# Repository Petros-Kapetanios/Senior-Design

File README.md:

# Senior‑Design

Zip files of my Gerber files for each PCB I created for my watt‑meter project.

## Order of Creation

1. **Capacitor Test Board**
2. **Current Transformer Test Board**
3. **Voltage Transformer Test Board**
4. **Low Pass‑V1**
5. **Low Pass‑V2**
6. **Final_Board‑Analog‑v1**
7. **Final_Board‑Analog‑v2**
8. **Final_Board‑Analog‑v3**
9. **Final_Board‑v1**
10. **Final_Board‑v2**
11. **Final_Board‑v3‑Triple‑Transformer**
12. **Final_Board‑v3B**
13. **Final_Board‑v3B‑Mark’s Copy**
14. **Final_Board‑v3C**
15. **Final_Board‑v3D**

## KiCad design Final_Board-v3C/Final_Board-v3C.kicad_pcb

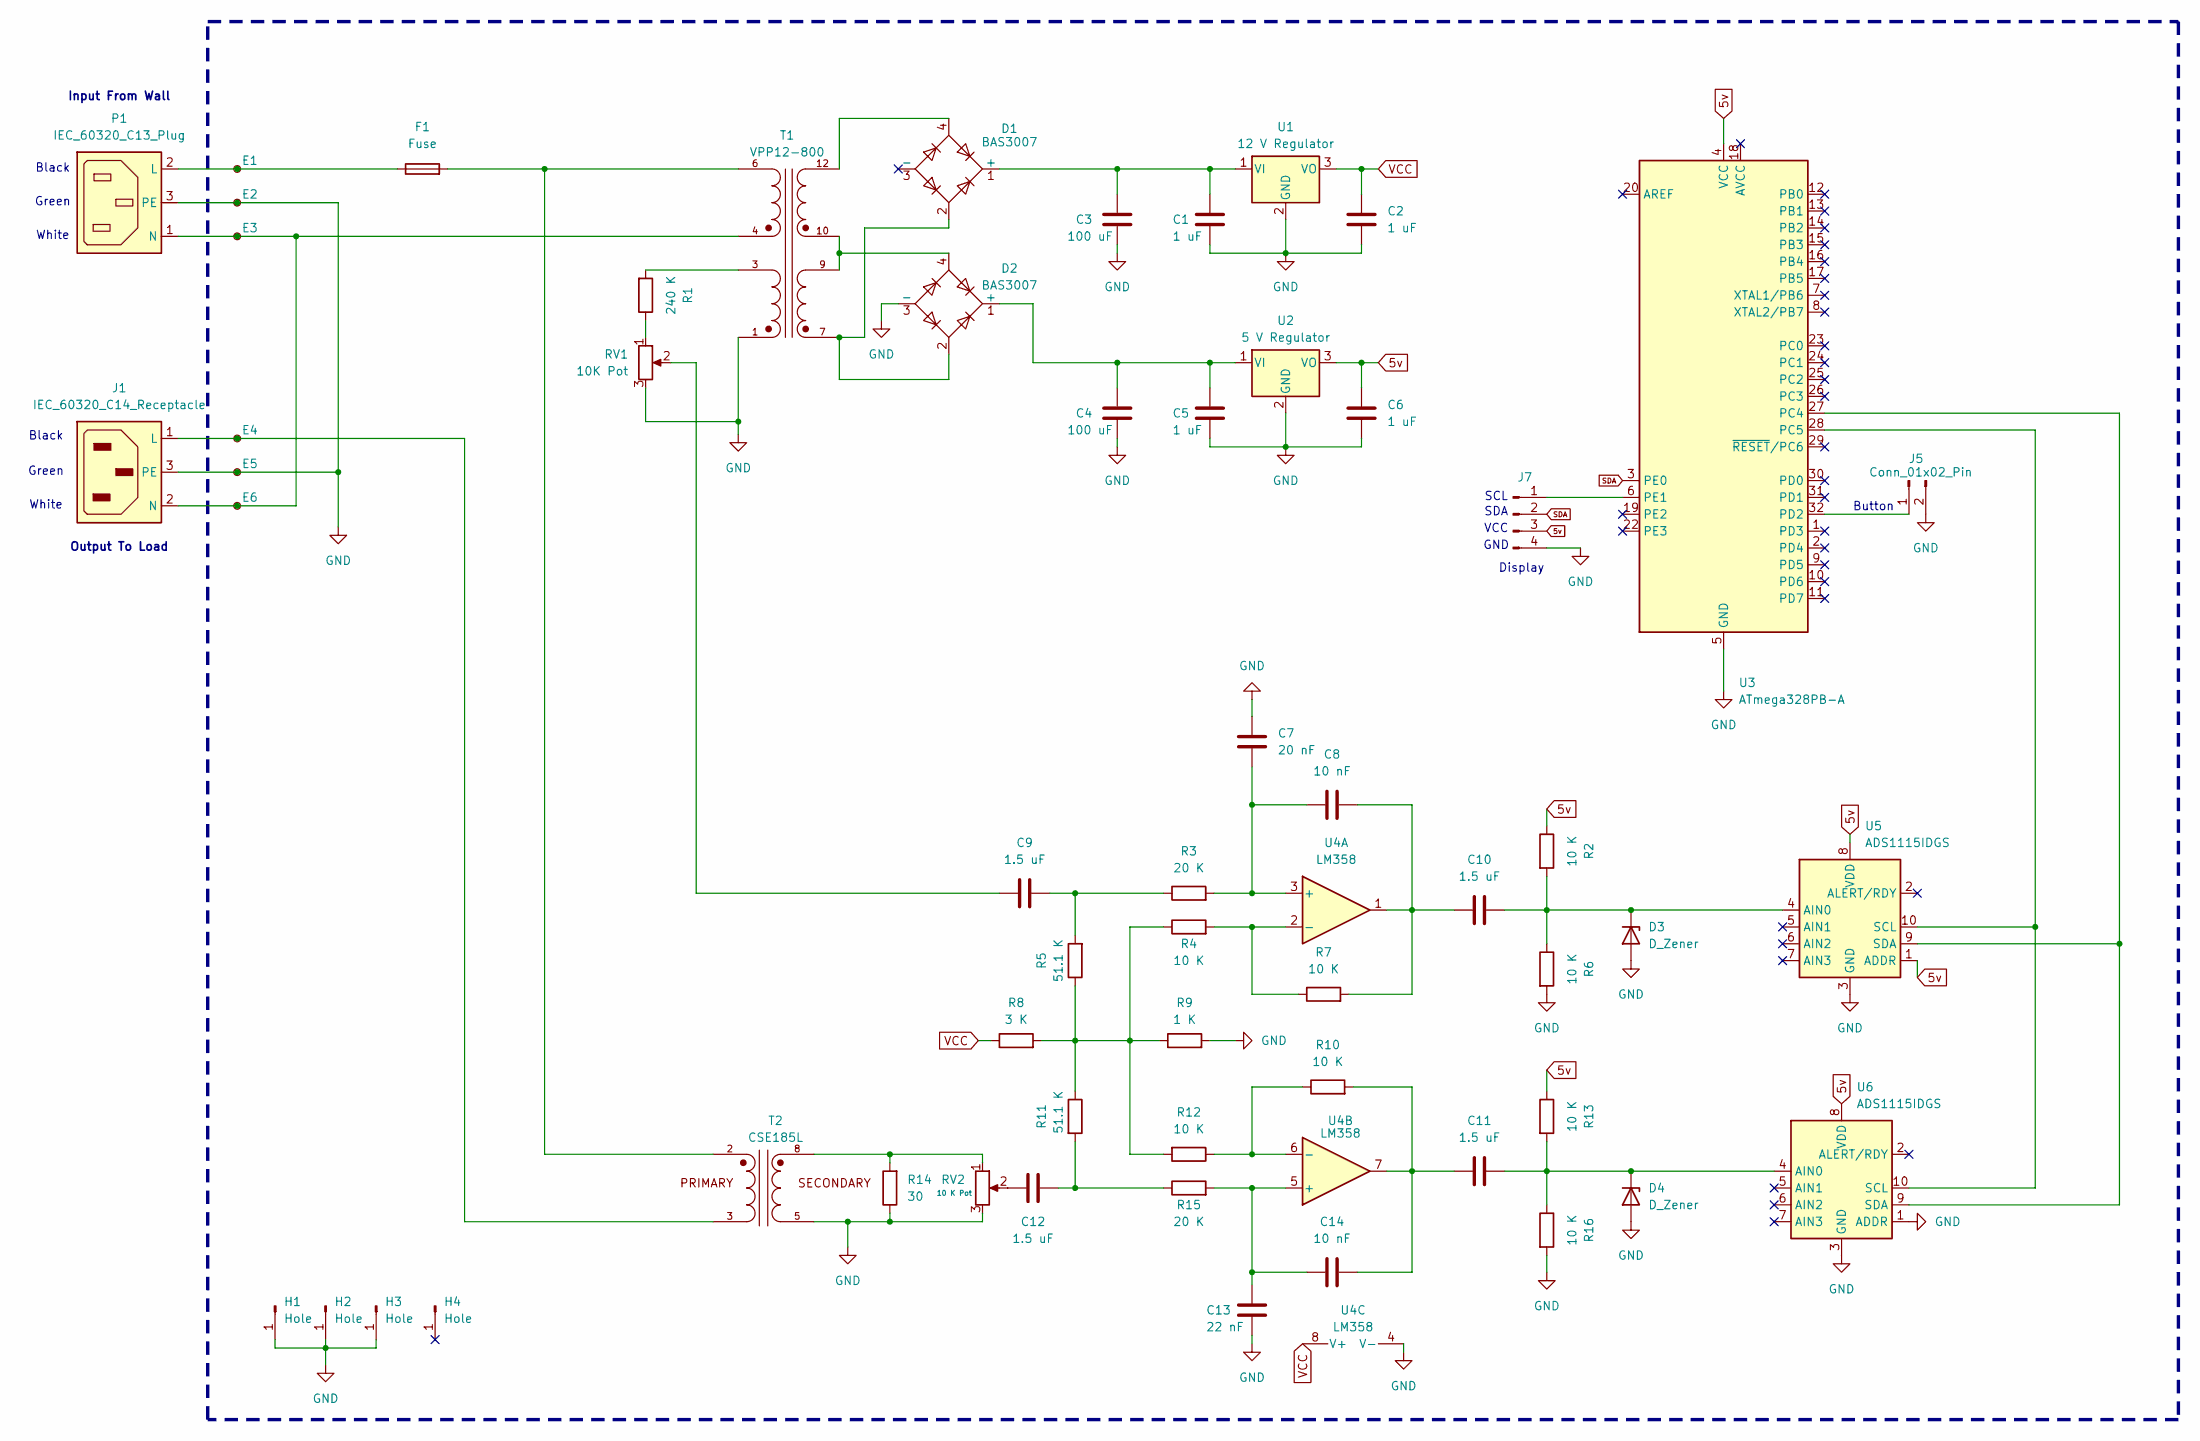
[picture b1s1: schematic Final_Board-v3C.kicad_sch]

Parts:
C1, C2, C5, C6: 1 uF; C_0805_2012Metric_Pad1.18x1.45mm_HandSolder
C3, C4: 100 uF; CP_Radial_D10.0mm_P5.00mm
C7: 20 nF; C_0805_2012Metric_Pad1.18x1.45mm_HandSolder
C8, C14: 10 nF; C_0805_2012Metric_Pad1.18x1.45mm_HandSolder
C9, C10, C11, C12: 1.5 uF; C_0805_2012Metric_Pad1.18x1.45mm_HandSolder
C13: 22 nF; C_0805_2012Metric_Pad1.18x1.45mm_HandSolder
D1, D2: BAS3007; SOT-143
D3, D4: D_Zener; D_SOD-123
E1, E2, E3, E4, E5, E6: TestPoint_Small; MountingHole_2.2mm_M2_ISO7380_Pad_TopBottom
F1: Fuse; Fuseholder_Keystone_3555-2
H1, H2, H3, H4: Hole; SolderWire-2sqmm_1x01_D2mm_OD3.9mm
J1: IEC_60320_C14_Receptacle
J5: Conn_01x02_Pin; PinHeader_1x02_P2.54mm_Vertical
J7: Conn_01x04_Pin; PinHeader_1x04_P2.54mm_Vertical
P1: IEC_60320_C13_Plug
R1: 240 K; R_1210_3225Metric
R2, R4, R6, R7, R10, R12, R13, R16: 10 K; R_0603_1608Metric
R3, R15: 20 K; R_0603_1608Metric
R5, R11: 51.1 K; R_0603_1608Metric
R8: 3 K; R_0603_1608Metric
R9: 1 K; R_0603_1608Metric
R14: 30; R_0603_1608Metric
RV1: 10K Pot; Potentiometer_Bourns_3296W_Vertical
RV2: 10 K Pot; Potentiometer_Bourns_3296W_Vertical
T1: VPP12-800; XFMR_VPP12-800
T2: CSE185L; XFMR_CSE185L; PARTREV N/A
U1: 12 V Regulator; TO-220-3_Vertical
U2: 5 V Regulator; TO-220-3_Vertical
U3: ATmega328PB-A; TQFP-32_7x7mm_P0.8mm
U4: LM358; DIP-8_W7.62mm_Socket
U5, U6: ADS1115IDGS; TSSOP-10_3x3mm_P0.5mm

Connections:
5v: C6.1, J7.3, R2.1, R13.1, U2.3 (VO), U3.4 (VCC), U5.1 (ADDR), U5.8 (VDD), U6.8 (VDD)
GND: C1.2, C2.2, C3.2, C4.2, C5.2, C6.2, C7.2, C13.1, D2.3 (-), D3.2 (A), D4.2 (A), E2.1, E5.1, H1.1, H2.1, H3.1, J1.3 (PE), J5.2, J7.4, P1.3 (PE), R6.2, R9.2, R14.1, R16.2, RV1.3, RV2.3, T1.1, T2.5, U1.2 (GND), U2.2 (GND), U3.5 (GND), U3.21 (GND), U4.4 (V-), U5.3 (GND), U6.1 (ADDR), U6.3 (GND)
unnamed: C9.1, RV1.2
unnamed: C9.2, R3.1, R5.2
unnamed: C8.2, C10.1, R7.2, U4.1
unnamed: C11.1, C14.2, R10.2, U4.7
unnamed: C12.1, RV2.2
unnamed: C12.2, R11.2, R15.1
unnamed: C1.1, C3.1, D1.1 (+), U1.1 (VI)
unnamed: D1.2, D2.2, T1.7
unnamed: D1.4, T1.12
unnamed: C4.1, C5.1, D2.1 (+), U2.1 (VI)
unnamed: D2.4, T1.9, T1.10
unnamed: C10.2, D3.1 (K), R2.2, R6.1, U5.4 (AIN0)
unnamed: C11.2, D4.1 (K), R13.2, R16.1, U6.4 (AIN0)
unnamed: F1.2, T1.6, T2.2
unnamed: E4.1, J1.1 (L), T2.3
unnamed: E3.1, E6.1, J1.2 (N), P1.1 (N), T1.4
unnamed: J5.1, U3.32 (PD2)
unnamed: J7.1, U3.6 (PE1)
unnamed: E1.1, F1.1, P1.2 (L)
unnamed: R1.1, RV1.1
unnamed: R1.2, T1.3
unnamed: R4.1, R5.1, R8.2, R9.1, R11.1, R12.2
unnamed: R14.2, RV2.1, T2.8
unnamed: U3.27 (PC4), U5.9 (SDA), U6.9 (SDA)
unnamed: U3.28 (PC5), U5.10 (SCL), U6.10 (SCL)
unnamed: C7.1, C8.1, R3.2, U4.3 (+)
unnamed: R4.2, R7.1, U4.2 (-)
unnamed: C13.2, C14.1, R15.2, U4.5 (+)
unnamed: R10.1, R12.1, U4.6 (-)
SDA: J7.2, U3.3 (PE0)
VCC: C2.1, R8.1, U1.3 (VO), U4.8 (V+)

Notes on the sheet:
Black
SDA
Green
Button
White
SCL
Input From Wall
VCC
GND
Display
Output To Load

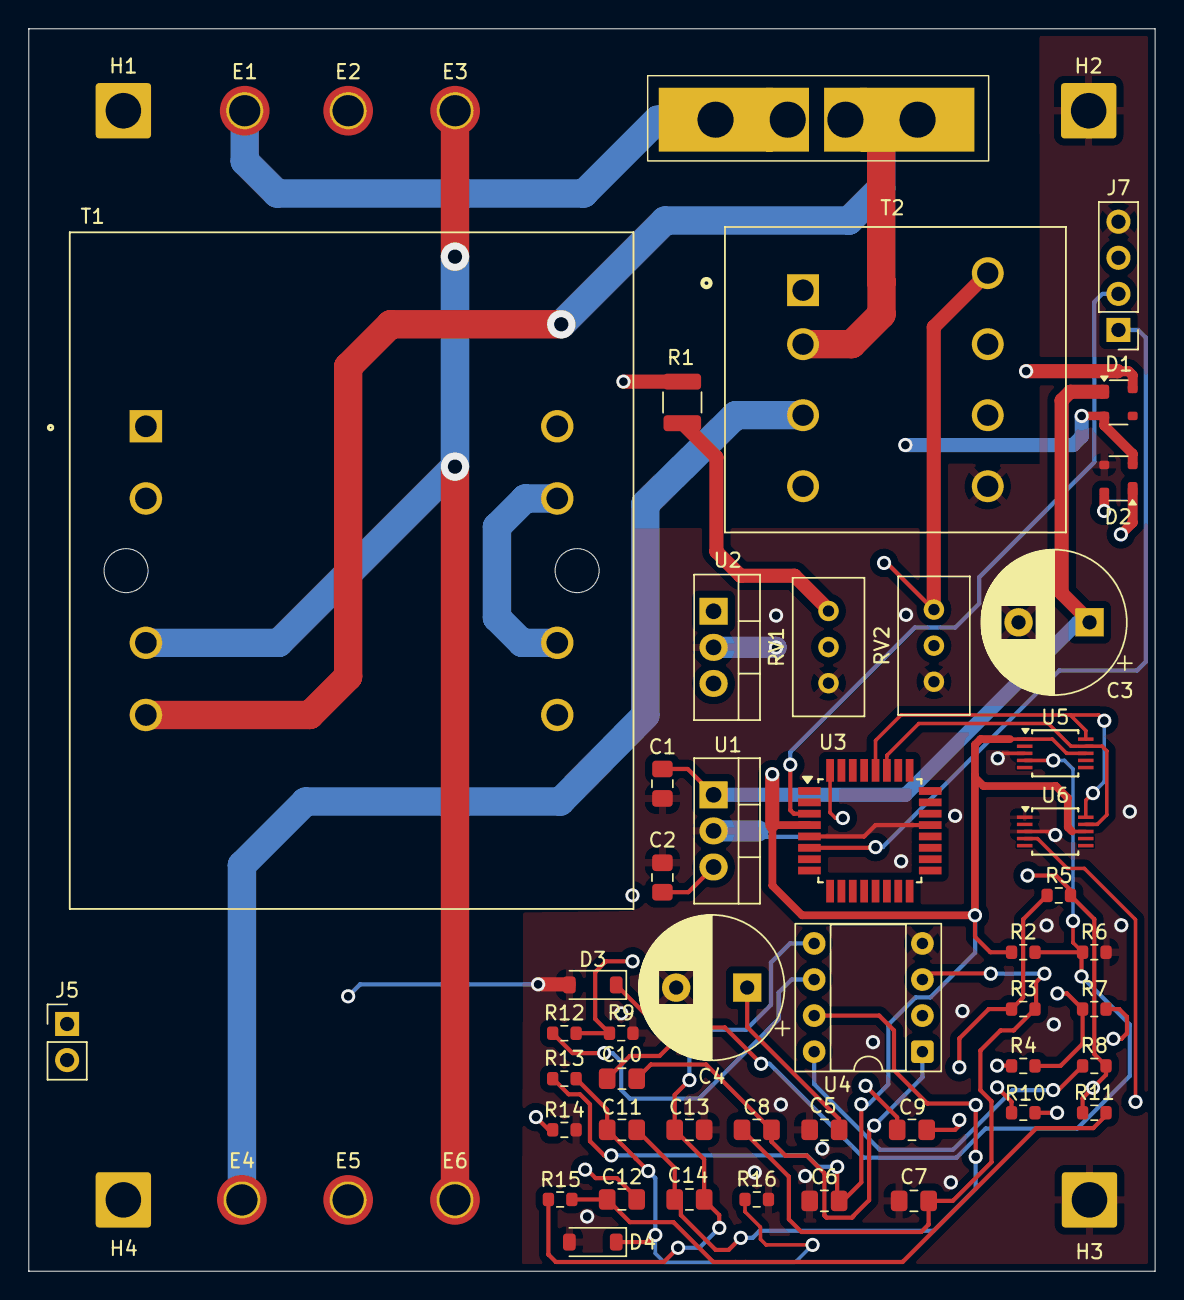
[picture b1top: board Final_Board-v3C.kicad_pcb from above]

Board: 4 copper layers, 79.3 x 87.5 mm, 57 parts (0 on the bottom side), 33 nets.

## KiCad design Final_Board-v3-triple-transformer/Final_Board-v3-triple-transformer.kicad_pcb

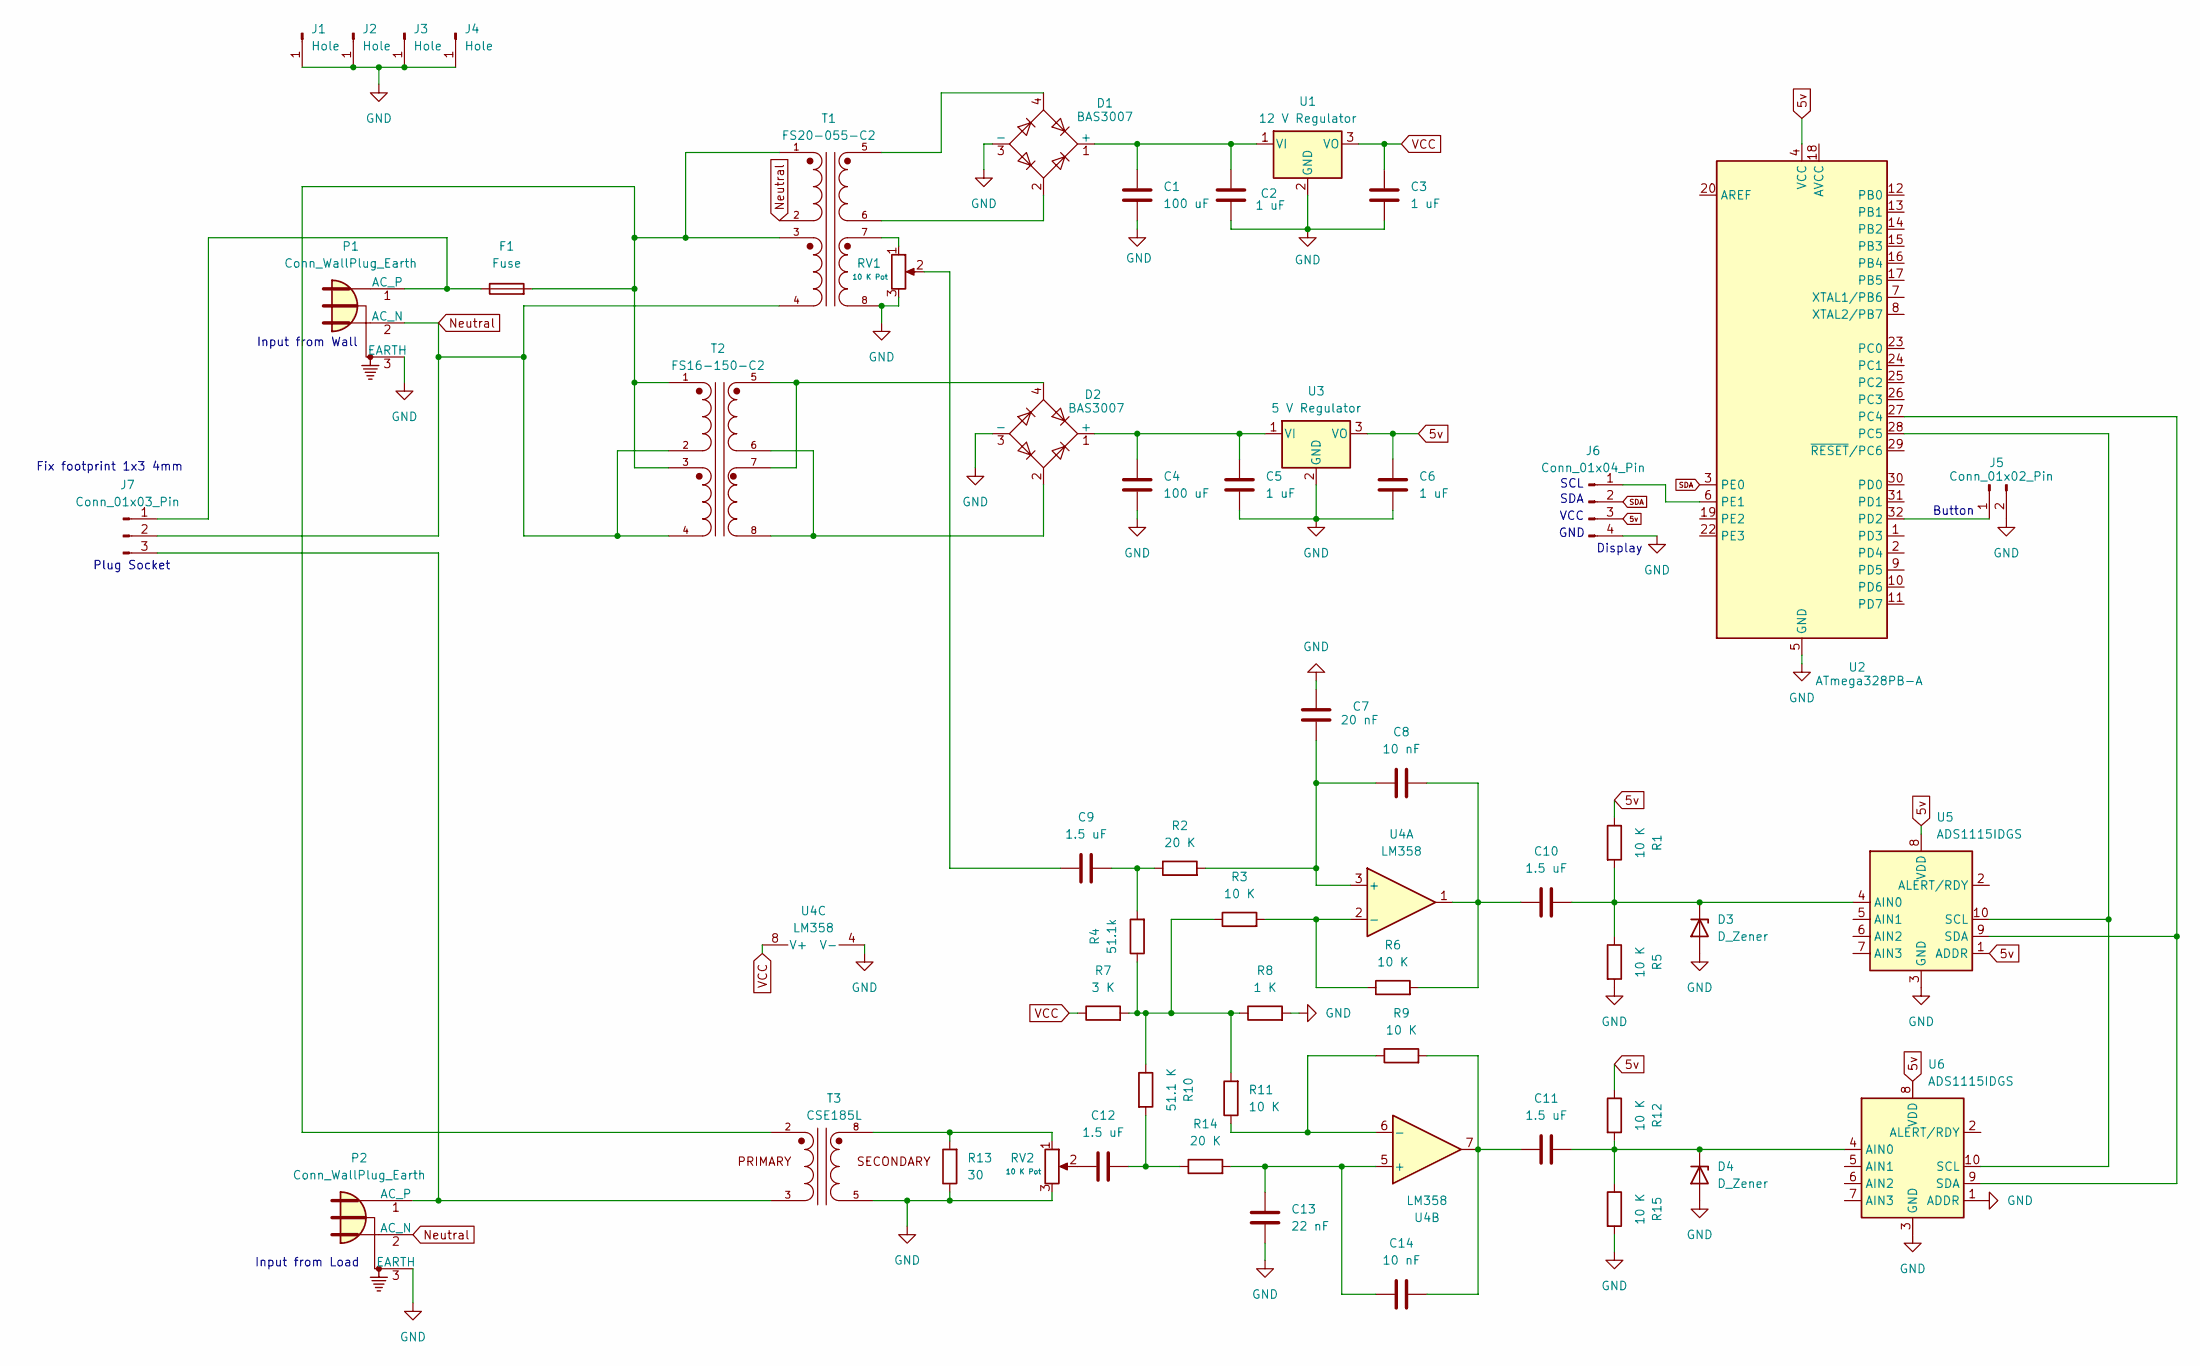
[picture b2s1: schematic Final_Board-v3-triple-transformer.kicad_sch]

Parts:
C1, C4: 100 uF; CP_Radial_D10.0mm_P5.00mm
C2, C3, C5, C6: 1 uF; C_0805_2012Metric_Pad1.18x1.45mm_HandSolder
C7: 20 nF; C_0805_2012Metric_Pad1.18x1.45mm_HandSolder
C8, C14: 10 nF; C_0805_2012Metric_Pad1.18x1.45mm_HandSolder
C9, C10, C11, C12: 1.5 uF; C_0805_2012Metric_Pad1.18x1.45mm_HandSolder
C13: 22 nF; C_0805_2012Metric_Pad1.18x1.45mm_HandSolder
D1, D2: BAS3007; SOT-143
D3, D4: D_Zener; D_SOD-123
F1: Fuse; Fuseholder_Keystone_3555-2
J1, J2, J3, J4: Hole; SolderWire-2sqmm_1x01_D2mm_OD3.9mm
J5: Conn_01x02_Pin; PinHeader_1x02_P2.00mm_Vertical
J6: Conn_01x04_Pin; PinHeader_1x04_P2.00mm_Vertical
J7: Conn_01x03_Pin; SolderWire-0.15sqmm_1x03_P4mm_D0.5mm_OD1.5mm
P1, P2: Conn_WallPlug_Earth
R1, R3, R5, R6, R9, R11, R12, R15: 10 K; R_0603_1608Metric
R2, R14: 20 K; R_0603_1608Metric
R4: 51.1k; R_0603_1608Metric
R7: 3 K; R_0603_1608Metric
R8: 1 K; R_0603_1608Metric
R10: 51.1 K; R_0603_1608Metric
R13: 30; R_0603_1608Metric
RV1, RV2: 10 K Pot; Potentiometer_Bourns_3296W_Vertical
T1: FS20-055-C2; XFMR_FS20-055-C2; PARTREV N/A
T2: FS16-150-C2; XFMR_FS16-150-C2; PARTREV N/A
T3: CSE185L; XFMR_CSE185L; PARTREV N/A
U1: 12 V Regulator; TO-220-3_Vertical
U2: ATmega328PB-A; TQFP-32_7x7mm_P0.8mm
U3: 5 V Regulator; TO-220-3_Vertical
U4: LM358; DIP-8_W7.62mm
U5, U6: ADS1115IDGS; VSSOP-10_3x3mm_P0.5mm

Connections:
5v: C6.1, J6.3, R1.1, R12.1, U2.4 (VCC), U3.3 (VO), U5.1 (ADDR), U5.8 (VDD), U6.8 (VDD)
GND: C1.2, C2.2, C3.2, C4.2, C5.2, C6.2, C7.2, C13.1, D1.3 (-), D2.3 (-), D3.2 (A), D4.2 (A), J1.1, J2.1, J3.1, J4.1, J5.2, J6.4, P1.3 (EARTH), P2.3 (EARTH), R5.2, R8.2, R13.1, R15.2, RV1.3, RV2.3, T1.8, T3.5, U1.2 (GND), U2.5 (GND), U2.21 (GND), U3.2 (GND), U4.4 (V-), U5.3 (GND), U6.1 (ADDR), U6.3 (GND)
unnamed: C9.1, RV1.2
unnamed: C9.2, R2.1, R4.2
unnamed: C8.2, C10.1, R6.2, U4.1
unnamed: C11.1, C14.2, R9.2, U4.7
unnamed: C12.1, RV2.2
unnamed: C12.2, R10.2, R14.1
unnamed: C1.1, C2.1, D1.1 (+), U1.1 (VI)
unnamed: D1.2, T1.6
unnamed: D1.4, T1.5
unnamed: C4.1, C5.1, D2.1 (+), U3.1 (VI)
unnamed: D2.2, T2.6, T2.8
unnamed: D2.4, T2.5, T2.7
unnamed: C10.2, D3.1 (K), R1.2, R5.1, U5.4 (AIN0)
unnamed: C11.2, D4.1 (K), R12.2, R15.1, U6.4 (AIN0)
unnamed: F1.2, T1.1, T1.3, T2.1, T2.3, T3.2
unnamed: J5.1, U2.32 (PD2)
unnamed: J6.1, U2.6 (PE1)
unnamed: F1.1, J7.1, P1.1 (AC_P)
unnamed: J7.3, P2.1 (AC_P), T3.3
unnamed: R3.1, R4.1, R7.2, R8.1, R10.1, R11.2
unnamed: R13.2, RV2.1, T3.8
unnamed: RV1.1, T1.7
unnamed: U2.27 (PC4), U5.9 (SDA), U6.9 (SDA)
unnamed: U2.28 (PC5), U5.10 (SCL), U6.10 (SCL)
unnamed: C7.1, C8.1, R2.2, U4.3 (+)
unnamed: R3.2, R6.1, U4.2 (-)
unnamed: C13.2, C14.1, R14.2, U4.5 (+)
unnamed: R9.1, R11.1, U4.6 (-)
Neutral: J7.2, P1.2 (AC_N), P2.2 (AC_N), T1.2, T1.4, T2.2, T2.4
SDA: J6.2, U2.3 (PE0)
VCC: C3.1, R7.1, U1.3 (VO), U4.8 (V+)

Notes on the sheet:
SDA
Plug Socket
Button
SCL
Input from Wall
VCC
GND
Fix footprint 1x3 4mm
Display
Input from Load

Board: 2 copper layers, 52 parts (1 on the bottom side), 33 nets, no tracks yet.

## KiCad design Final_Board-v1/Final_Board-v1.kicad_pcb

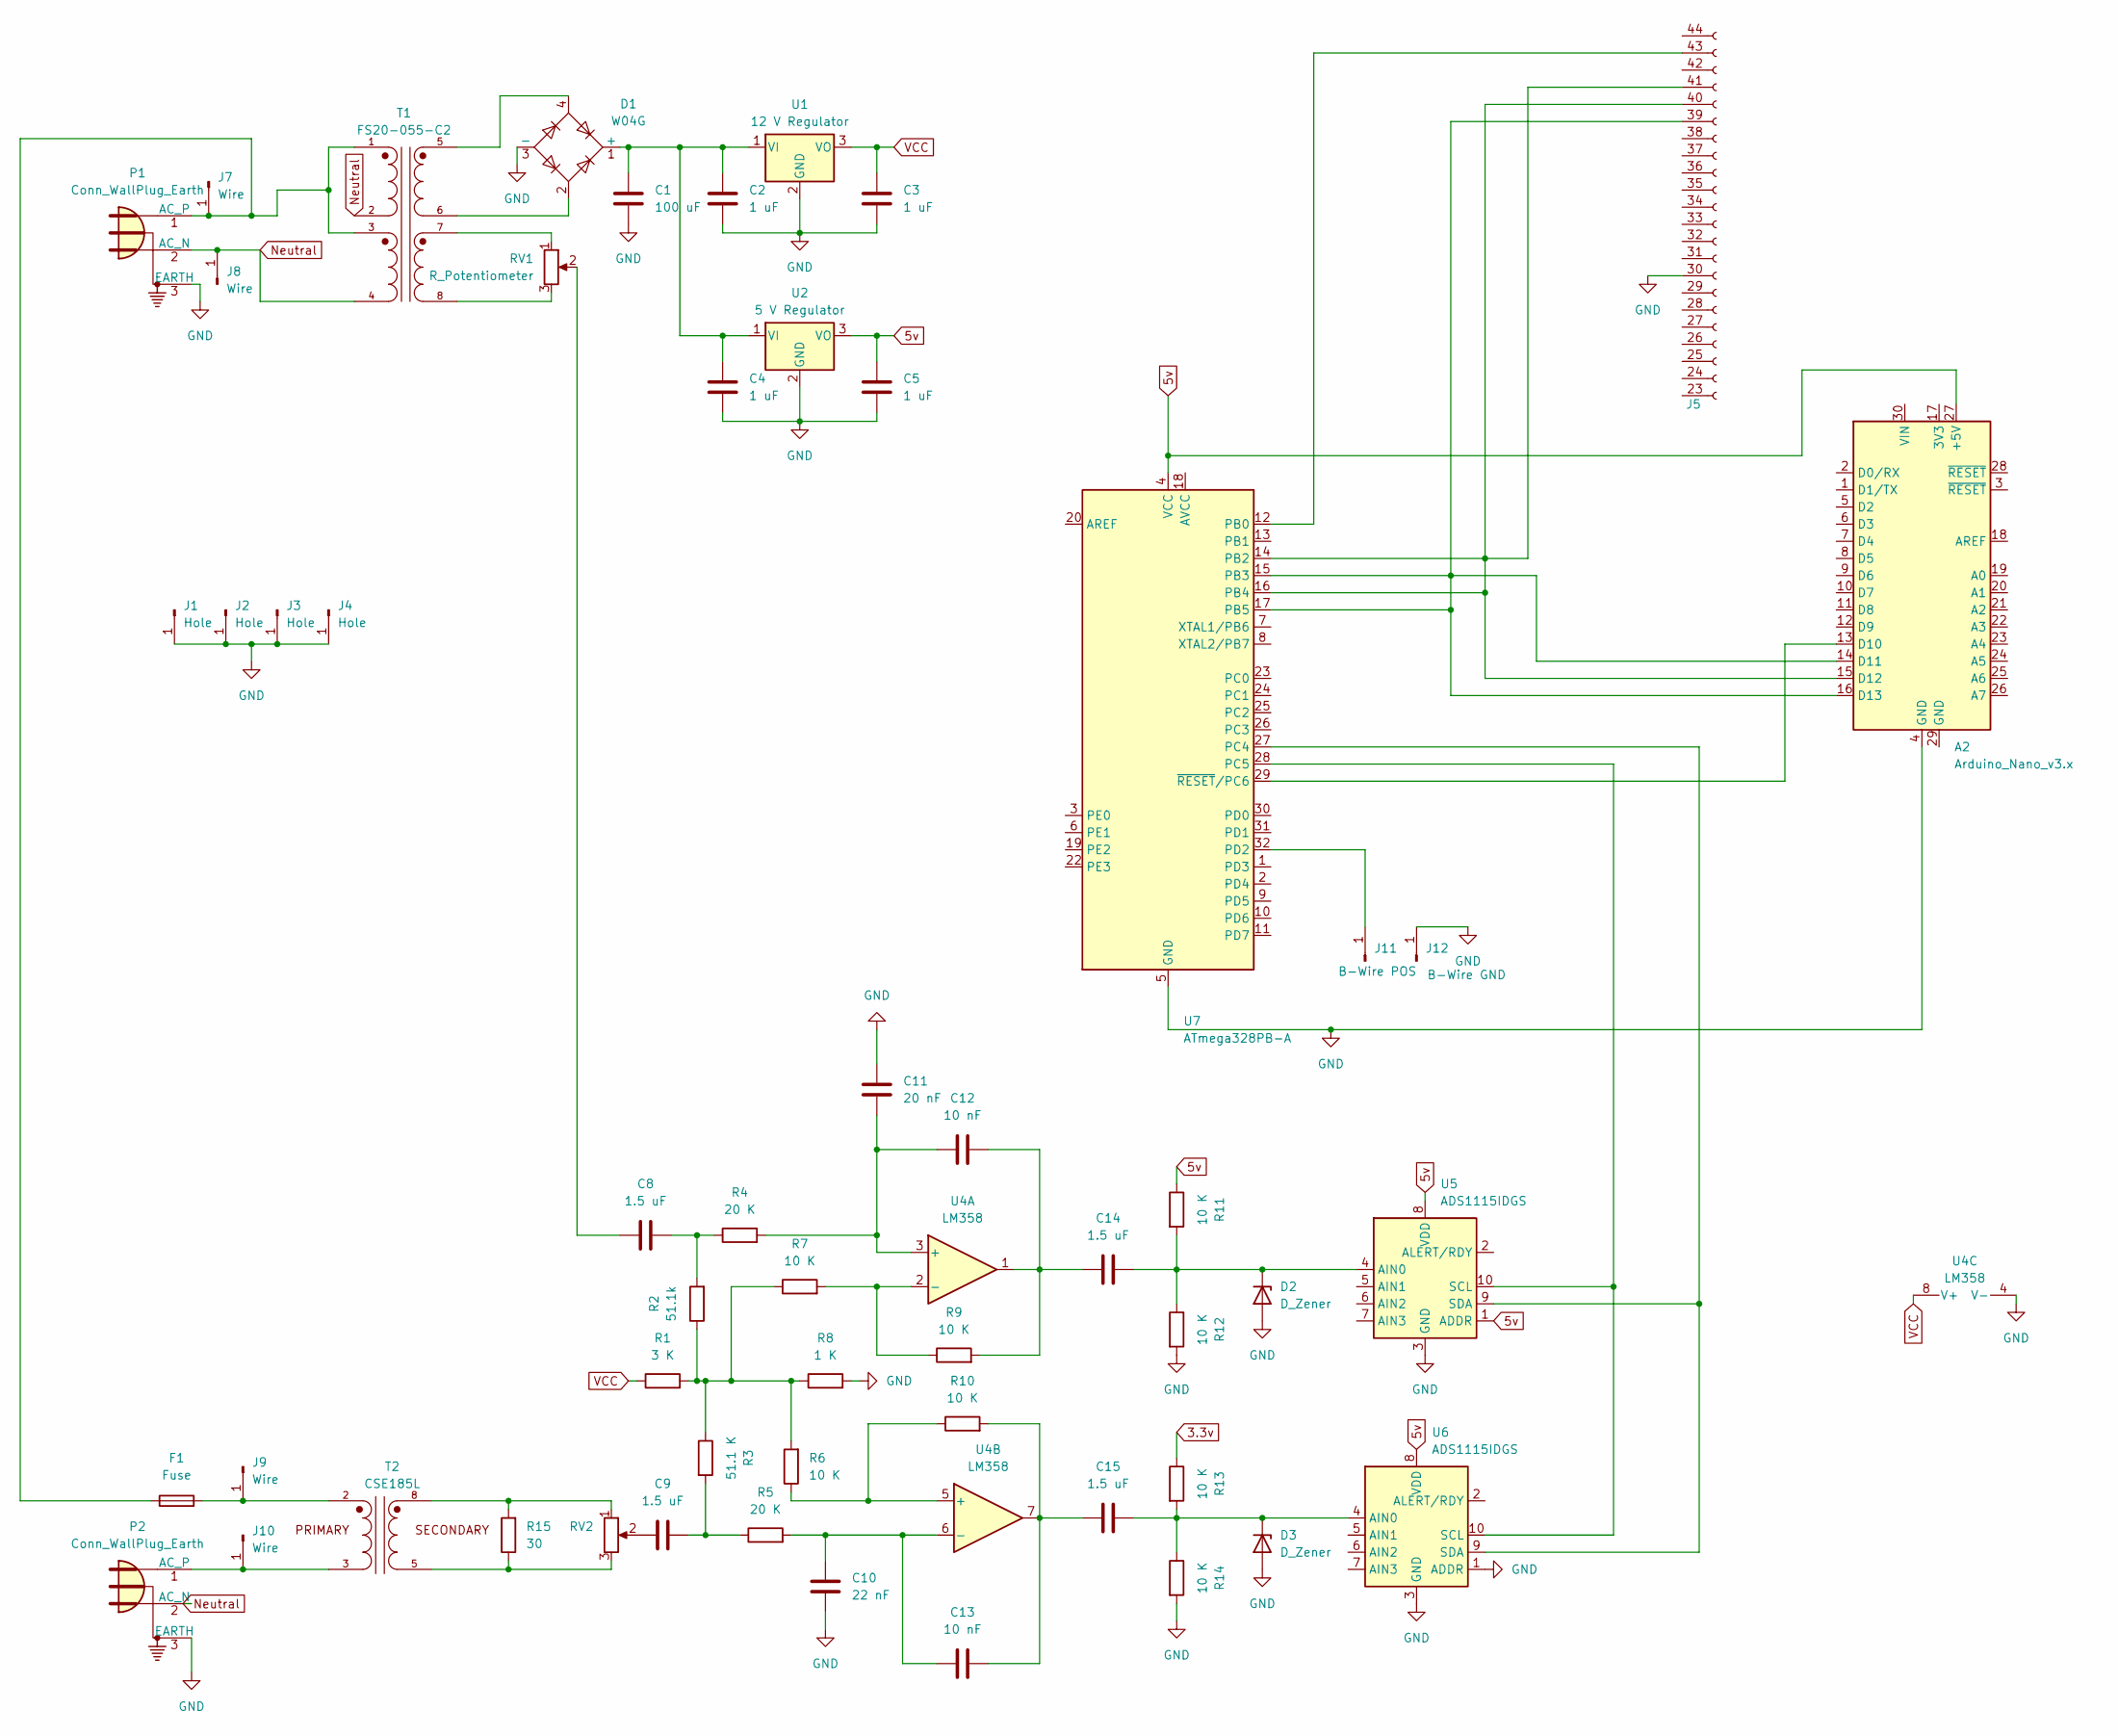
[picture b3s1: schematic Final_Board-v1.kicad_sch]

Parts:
A2: Arduino_Nano_v3.x; Arduino_Nano
C1: 100 uF; CP_Radial_D10.0mm_P5.00mm
C2, C3, C4, C5: 1 uF; C_Disc_D4.7mm_W2.5mm_P5.00mm
C8, C9, C14, C15: 1.5 uF; C_Rect_L7.2mm_W5.5mm_P5.00mm_FKS2_FKP2_MKS2_MKP2
C10: 22 nF; C_Disc_D4.7mm_W2.5mm_P5.00mm
C11: 20 nF; C_Rect_L7.5mm_W6.5mm_P5.00mm
C12, C13: 10 nF; C_Disc_D4.7mm_W2.5mm_P5.00mm
D1: W04G; Diode_Bridge_Round_D9.8mm
D2, D3: D_Zener; D_A-405_P10.16mm_Horizontal
F1: Fuse
J1, J2, J3, J4: Hole; SolderWire-2sqmm_1x01_D2mm_OD3.9mm
J5: Conn_01x22_Socket; PinSocket_1x22_P2.54mm_Vertical
J7, J8, J9, J10: Wire; SolderWire-2sqmm_1x01_D2mm_OD3.9mm
J11: B-Wire POS; SolderWire-2sqmm_1x01_D2mm_OD3.9mm
J12: B-Wire GND; SolderWire-2sqmm_1x01_D2mm_OD3.9mm
P1, P2: Conn_WallPlug_Earth
R1: 3 K; R_Axial_DIN0207_L6.3mm_D2.5mm_P10.16mm_Horizontal
R2: 51.1k; R_Axial_DIN0207_L6.3mm_D2.5mm_P10.16mm_Horizontal
R3: 51.1 K; R_Axial_DIN0207_L6.3mm_D2.5mm_P10.16mm_Horizontal
R4, R5: 20 K; R_Axial_DIN0207_L6.3mm_D2.5mm_P10.16mm_Horizontal
R6, R7, R9, R10, R14: 10 K; R_Axial_DIN0207_L6.3mm_D2.5mm_P10.16mm_Horizontal
R8: 1 K; R_1206_3216Metric
R11, R12, R13: 10 K; R_1206_3216Metric
R15: 30; R_Axial_DIN0207_L6.3mm_D2.5mm_P10.16mm_Horizontal
RV1, RV2: R_Potentiometer; Potentiometer_ACP_CA6-H2,5_Horizontal
T1: FS20-055-C2; XFMR_FS20-055-C2; PARTREV N/A
T2: CSE185L; XFMR_CSE185L; PARTREV N/A
U1: 12 V Regulator; TO-220-3_Vertical
U2: 5 V Regulator; TO-220-3_Vertical
U4: LM358; DIP-8_W7.62mm
U5, U6: ADS1115IDGS; TSSOP-10_3x3mm_P0.5mm
U7: ATmega328PB-A; TQFP-32_7x7mm_P0.8mm

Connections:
3.3v: R13.1; also elsewhere on the board
5v: A2.27 (+5V), C5.1, R11.1, U2.3 (VO), U5.1 (ADDR), U5.8 (VDD), U6.8 (VDD), U7.4 (VCC)
GND: A2.4 (GND), C1.2, C2.2, C3.2, C4.2, C5.2, C10.1, C11.2, D1.3 (-), D2.2 (A), D3.2 (A), J1.1, J2.1, J3.1, J4.1, J5.30, J12.1, P1.3 (EARTH), P2.3 (EARTH), R8.2, R12.2, R14.2, U1.2 (GND), U2.2 (GND), U4.4 (V-), U5.3 (GND), U6.1 (ADDR), U6.3 (GND), U7.5 (GND), U7.21 (GND); also elsewhere on the board
unnamed: A2.13 (D10), U7.29 (~RESET/PC6)
unnamed: A2.14 (D11), A2.16 (D13), J5.39, U7.15 (PB3), U7.17 (PB5)
unnamed: A2.15 (D12), J5.40, J5.41, U7.14 (PB2), U7.16 (PB4)
unnamed: C8.1, RV1.2
unnamed: C8.2, R2.2, R4.1
unnamed: C9.1, RV2.2
unnamed: C9.2, R3.2, R5.1
unnamed: C12.2, C14.1, R9.2, U4.1
unnamed: C13.2, C15.1, R10.2, U4.7
unnamed: C1.1, C2.1, C4.1, D1.1 (+), U1.1 (VI), U2.1 (VI)
unnamed: D1.2, T1.6
unnamed: D1.4, T1.5
unnamed: C14.2, D2.1 (K), R11.2, R12.1, U5.4 (AIN0)
unnamed: C15.2, D3.1 (K), R13.2, R14.1, U6.4 (AIN0)
unnamed: J5.43, U7.12 (PB0)
unnamed: F1.1, J7.1, P1.1 (AC_P), T1.1, T1.3
unnamed: F1.2, J9.1, T2.2
unnamed: J10.1, P2.1 (AC_P), T2.3
unnamed: J11.1, U7.32 (PD2)
unnamed: R1.2, R2.1, R3.1, R6.2, R7.1, R8.1
unnamed: R15.1, RV2.3, T2.5
unnamed: R15.2, RV2.1, T2.8
unnamed: RV1.1, T1.7
unnamed: RV1.3, T1.8
unnamed: C11.1, C12.1, R4.2, U4.3 (+)
unnamed: R7.2, R9.1, U4.2 (-)
unnamed: R6.1, R10.1, U4.5 (+)
unnamed: C10.2, C13.1, R5.2, U4.6 (-)
unnamed: U5.10 (SCL), U6.10 (SCL), U7.28 (PC5)
unnamed: U5.9 (SDA), U6.9 (SDA), U7.27 (PC4)
Neutral: J8.1, P1.2 (AC_N), P2.2 (AC_N), T1.2, T1.4
VCC: C3.1, R1.1, U1.3 (VO), U4.8 (V+)

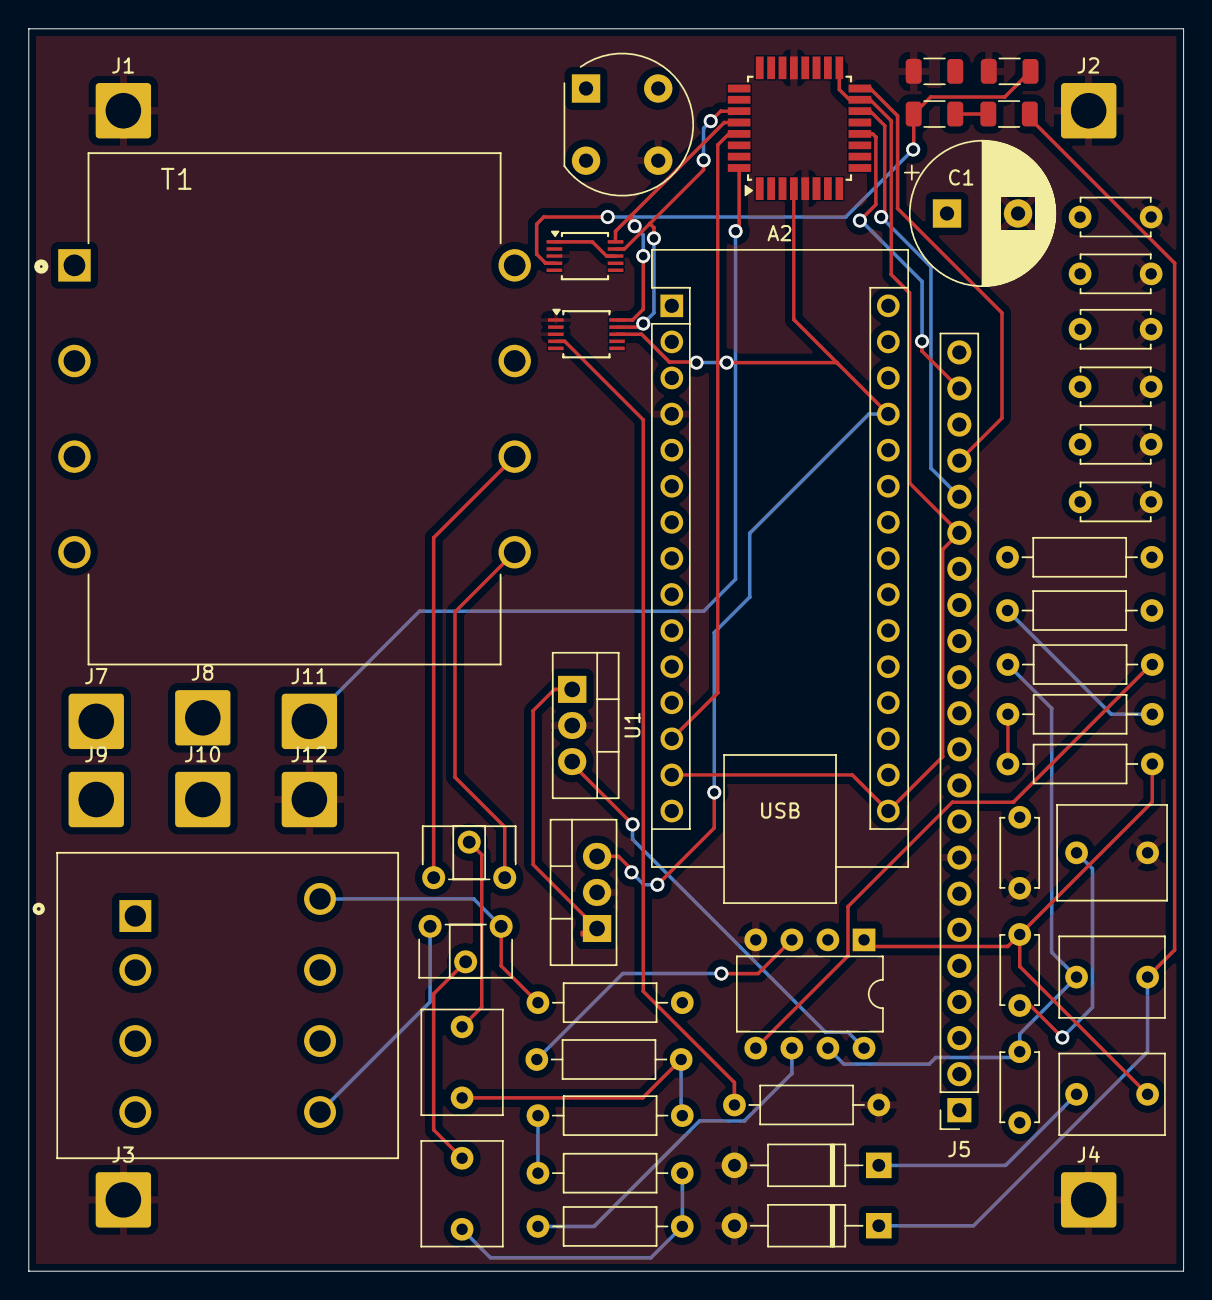
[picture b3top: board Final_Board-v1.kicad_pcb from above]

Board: 2 copper layers, 81.3 x 87.5 mm, 55 parts (0 on the bottom side), 35 nets.

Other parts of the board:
C6, C7: 1 uF; C_Disc_D4.7mm_W2.5mm_P5.00mm

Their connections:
3.3v: C6.1, C7.1; also elsewhere on the board
GND: C6.2, C7.2; also elsewhere on the board

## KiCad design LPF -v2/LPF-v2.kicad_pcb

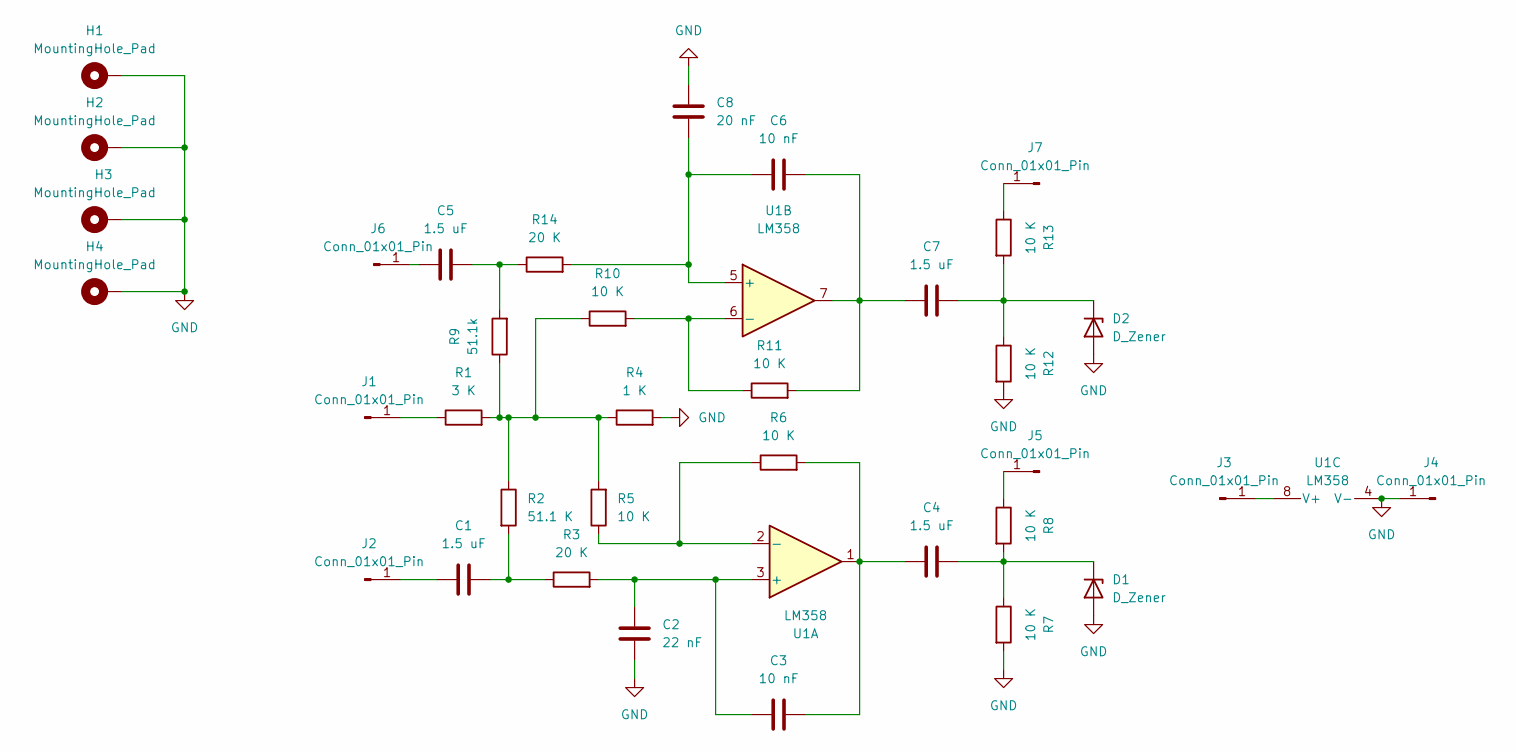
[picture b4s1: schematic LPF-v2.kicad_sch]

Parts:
C1, C4, C5, C7: 1.5 uF; C_Rect_L7.2mm_W5.5mm_P5.00mm_FKS2_FKP2_MKS2_MKP2
C2: 22 nF; C_Rect_L7.5mm_W6.5mm_P5.00mm
C3: 10 nF; C_Disc_D7.5mm_W5.0mm_P5.00mm
C6: 10 nF; C_Rect_L7.2mm_W5.5mm_P5.00mm_FKS2_FKP2_MKS2_MKP2
C8: 20 nF; C_Rect_L7.5mm_W6.5mm_P5.00mm
D1, D2: D_Zener; D_A-405_P10.16mm_Horizontal
H1, H2, H3, H4: MountingHole_Pad; MountingHole_3.2mm_M3_DIN965_Pad_TopBottom
J1, J2, J3, J4, J5, J6, J7: Conn_01x01_Pin; PinHeader_1x01_P2.54mm_Vertical
R1: 3 K; R_Axial_DIN0207_L6.3mm_D2.5mm_P10.16mm_Horizontal
R2: 51.1 K; R_Axial_DIN0207_L6.3mm_D2.5mm_P10.16mm_Horizontal
R3, R14: 20 K; R_Axial_DIN0207_L6.3mm_D2.5mm_P10.16mm_Horizontal
R4: 1 K; R_Axial_DIN0207_L6.3mm_D2.5mm_P10.16mm_Horizontal
R5, R6, R7, R8, R10, R11, R12, R13: 10 K; R_Axial_DIN0207_L6.3mm_D2.5mm_P10.16mm_Horizontal
R9: 51.1k; R_Axial_DIN0207_L6.3mm_D2.5mm_P10.16mm_Horizontal
U1: LM358; DIP-8_W7.62mm

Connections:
GND: C2.1, C8.2, D1.2 (A), D2.2 (A), H1.1, H2.1, H3.1, H4.1, J4.1, R4.2, R7.2, R12.2, U1.4 (V-)
unnamed: C1.2, R2.2, R3.1
unnamed: C3.2, C4.1, R6.2, U1.1
unnamed: C5.2, R9.2, R14.1
unnamed: C6.2, C7.1, R11.2, U1.7
unnamed: C4.2, D1.1 (K), R7.1, R8.2
unnamed: C7.2, D2.1 (K), R12.1, R13.2
unnamed: J1.1, R1.1
unnamed: C1.1, J2.1
unnamed: J3.1, U1.8 (V+)
unnamed: J5.1, R8.1
unnamed: C5.1, J6.1
unnamed: J7.1, R13.1
unnamed: R1.2, R2.1, R4.1, R5.2, R9.1, R10.1
unnamed: C2.2, C3.1, R3.2, U1.3 (+)
unnamed: R5.1, R6.1, U1.2 (-)
unnamed: C6.1, C8.1, R14.2, U1.5 (+)
unnamed: R10.2, R11.1, U1.6 (-)

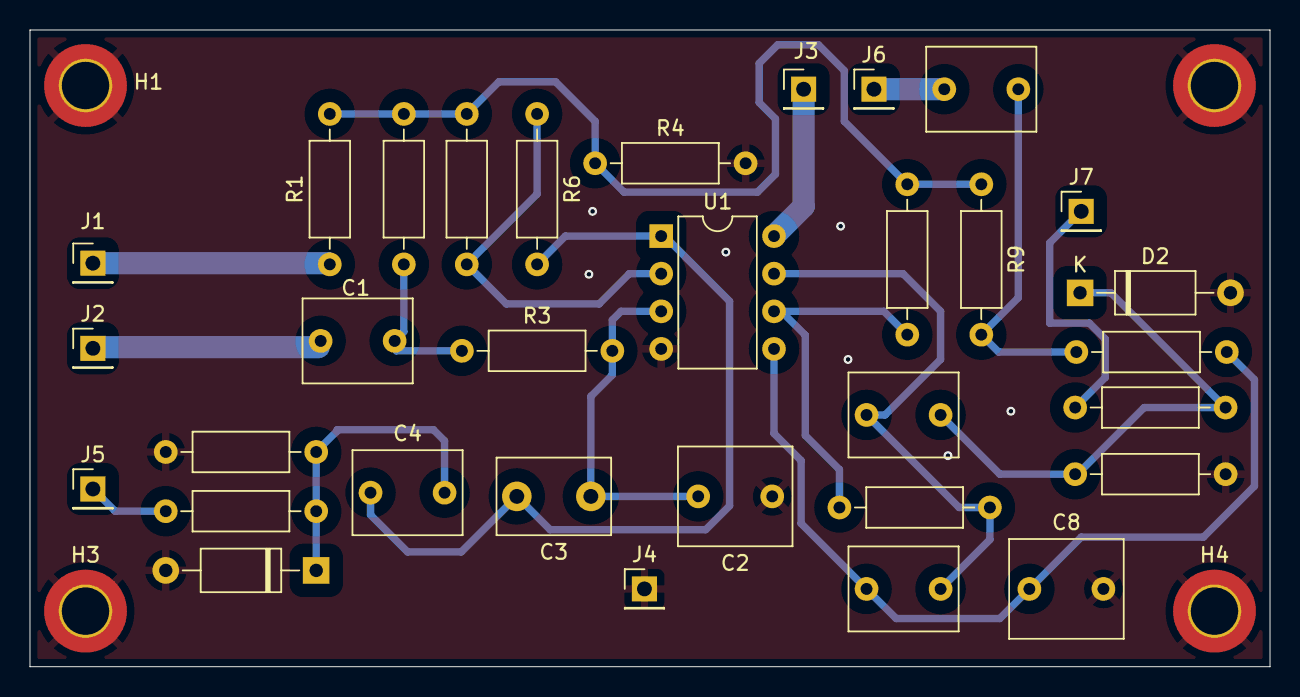
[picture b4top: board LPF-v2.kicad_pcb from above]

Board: 2 copper layers, 83.8 x 43.0 mm, 36 parts (0 on the bottom side), 18 nets.

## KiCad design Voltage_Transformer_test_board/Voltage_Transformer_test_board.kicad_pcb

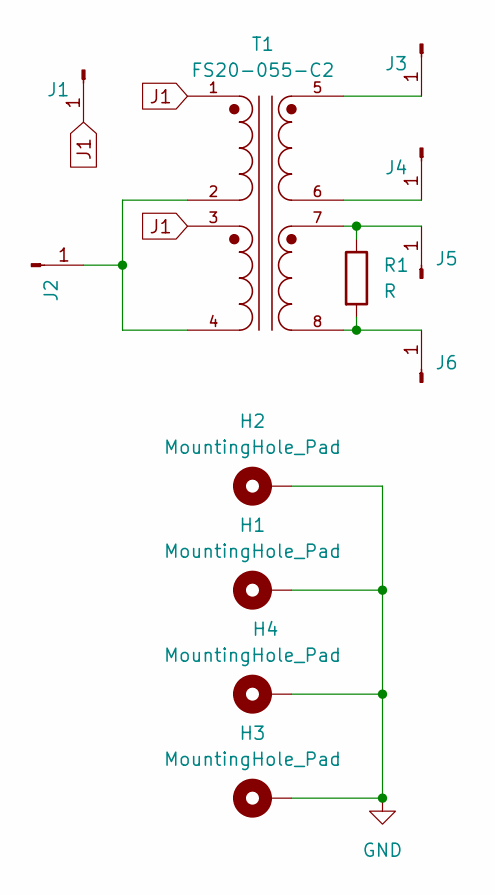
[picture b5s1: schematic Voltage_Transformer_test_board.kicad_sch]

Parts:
H1, H2, H3, H4: MountingHole_Pad; MountingHole_3.2mm_M3_DIN965_Pad_TopBottom
J1, J2, J3, J4, J5, J6: Conn_01x01_Pin; SolderWire-2sqmm_1x01_D2mm_OD3.9mm
R1: R; R_Axial_DIN0207_L6.3mm_D2.5mm_P10.16mm_Horizontal
T1: FS20-055-C2; XFMR_FS20-055-C2; PARTREV N/A

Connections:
GND: H1.1, H2.1, H3.1, H4.1
J1: J1.1, T1.1, T1.3
unnamed: J2.1, T1.2, T1.4
unnamed: J3.1, T1.5
unnamed: J4.1, T1.6
unnamed: J5.1, R1.1, T1.7
unnamed: J6.1, R1.2, T1.8
